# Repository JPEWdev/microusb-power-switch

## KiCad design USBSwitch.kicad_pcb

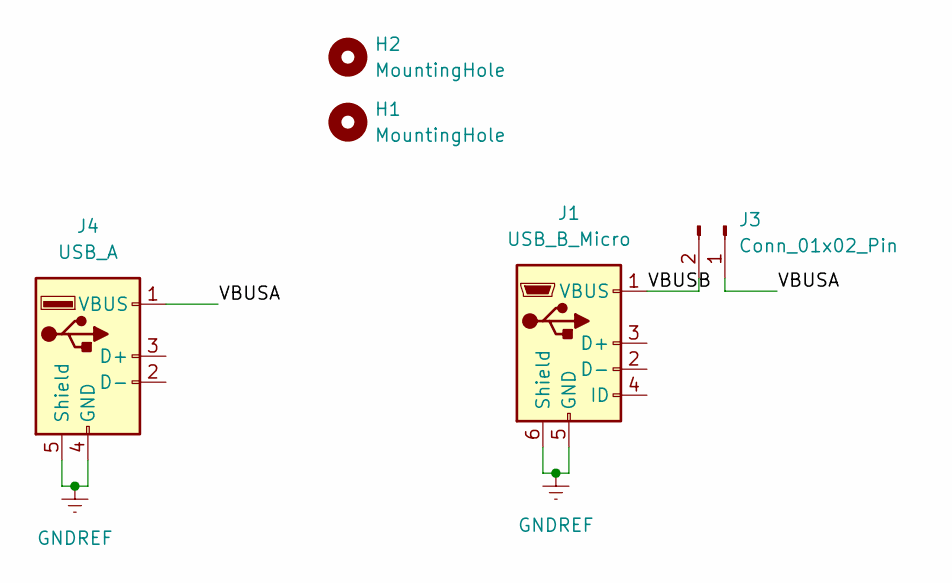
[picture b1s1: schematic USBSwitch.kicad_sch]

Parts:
H1, H2: MountingHole; MountingHole_3.2mm_M3_Pad_TopBottom
J1: USB_B_Micro; USB_Micro-B_Wuerth_629105150521
J3: Conn_01x02_Pin; PinHeader_1x02_P2.54mm_Vertical
J4: USB_A; USB_A_Molex_67643_Horizontal

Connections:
/VBUSA: J3.1, J4.1 (VBUS)
/VBUSB: J1.1 (VBUS), J3.2
GNDREF: J1.5 (GND), J1.6 (Shield), J4.4 (GND), J4.5 (Shield)

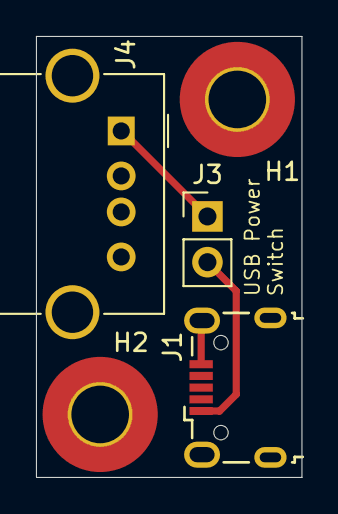
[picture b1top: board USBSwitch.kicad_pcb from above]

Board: 2 copper layers, 14.8 x 24.5 mm, 5 parts (0 on the bottom side), 3 nets.

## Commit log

2024-12-24 Initial Commit
    The initial design
2024-12-31 Replace one micro-USB with USB-A
    It's surprisingly hard to find micro-USB to micro-USB cables that can
    handle full USB 2.0 current, so replace one of the connectors with a
    USB-A since USB-A to micro-USB cables are plentiful
